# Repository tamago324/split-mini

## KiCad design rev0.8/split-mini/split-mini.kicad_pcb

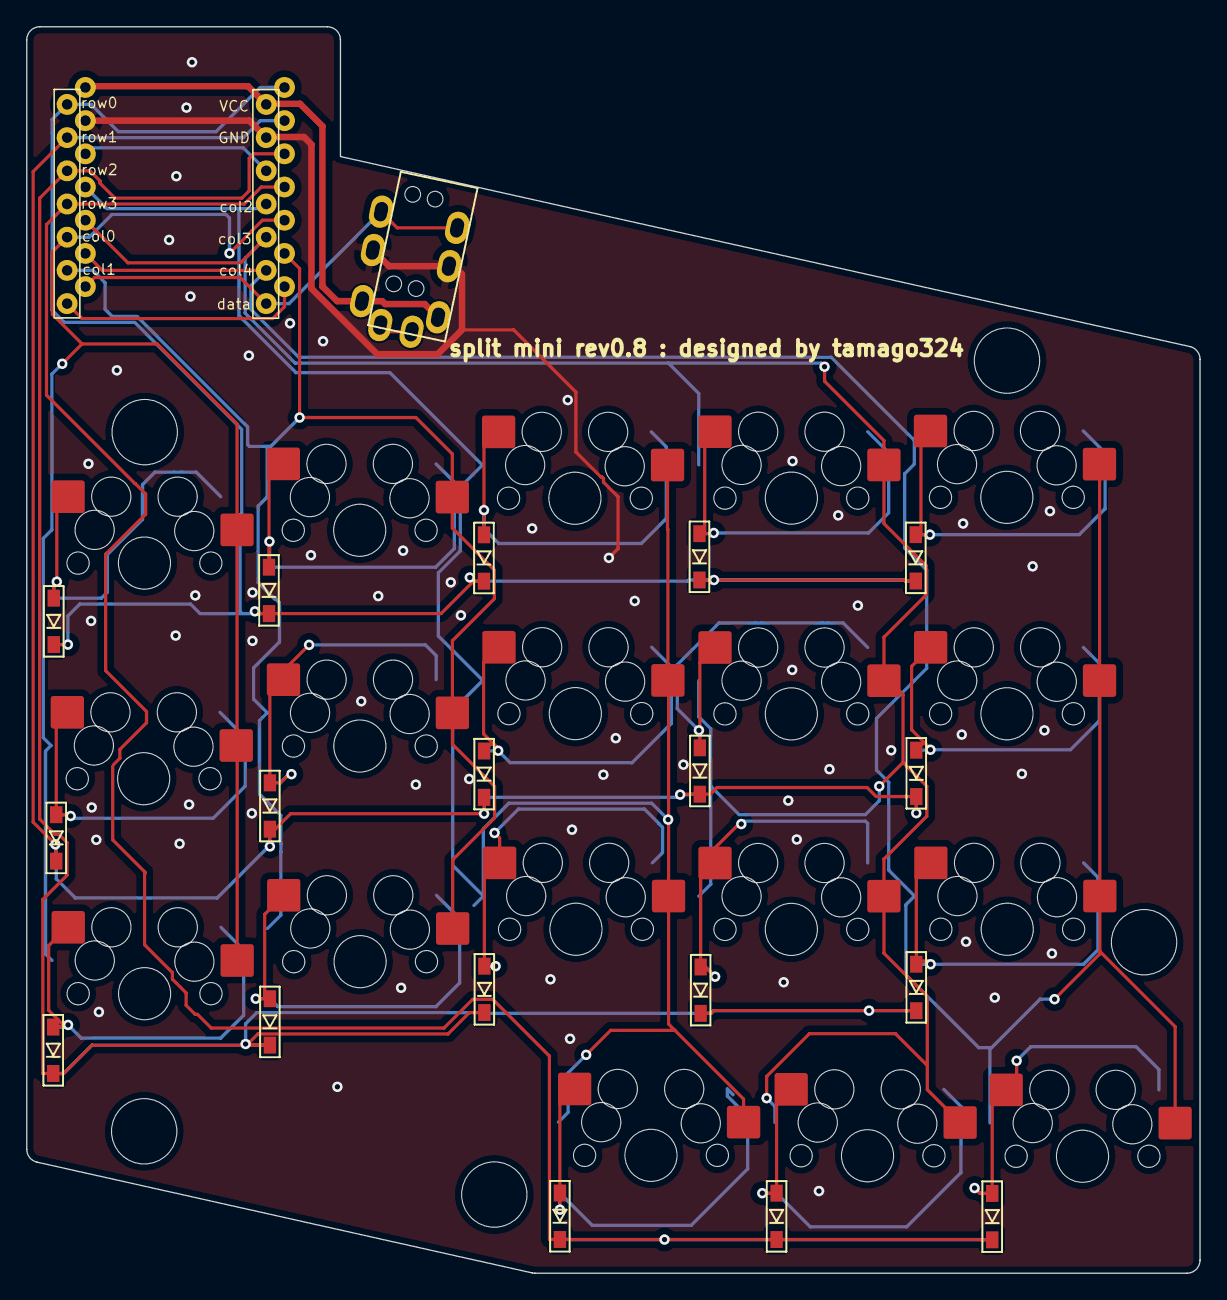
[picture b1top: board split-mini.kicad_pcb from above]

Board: 2 copper layers, 89.8 x 95.4 mm, 43 parts (0 on the bottom side), 30 nets.

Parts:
D1, D2, D3, D4, D5, D6, D7, D8, D9, D10, D11, D12, D13, D14, D15, D16, D17, D18: D; D3_SMD
HOLE1, HOLE2, HOLE3, HOLE5: Val**; M2_HOLE_v2_4.5mm
HOLE4: Val*; M2_HOLE_v2_4.5mm
J1: MJ-4PP-9
SW1, SW2, SW3, SW4, SW5, SW6, SW7, SW8, SW9, SW10, SW11, SW12, SW13, SW14, SW15, SW16, SW17, SW18: SW_PUSH; MX-Hotswap-1U
U1: Seeed Studio XIAO SAMD21; XIAO-RP2040_mod

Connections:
GND: J1.C, U1.13 (GND)
unnamed: D1.2 (A), SW1.2
unnamed: D2.2 (A), SW2.2
unnamed: D3.2 (A), SW3.2
unnamed: D4.2 (A), SW4.2
unnamed: D5.2 (A), SW5.2
unnamed: D6.2 (A), SW6.2
unnamed: D7.2 (A), SW7.2
unnamed: D8.2 (A), SW8.2
unnamed: D9.2 (A), SW9.2
unnamed: D10.2 (A), SW10.2
unnamed: D11.2 (A), SW11.2
unnamed: D12.2 (A), SW12.2
unnamed: D13.2 (A), SW13.2
unnamed: D14.2 (A), SW14.2
unnamed: D15.2 (A), SW15.2
unnamed: D16.2 (A), SW16.2
unnamed: D17.2 (A), SW17.2
unnamed: D18.2 (A), SW18.2
VCC: J1.D, U1.14 (5V)
col0: SW1.1, SW6.1, SW11.1, U1.5 (GP6_SDA)
col1: SW2.1, SW7.1, SW12.1, U1.6 (GP7_SCL)
col2: SW3.1, SW8.1, SW13.1, SW16.1, U1.11 (GP3)
col3: SW4.1, SW9.1, SW14.1, SW17.1, U1.10 (GP4)
col4: SW5.1, SW10.1, SW15.1, SW18.1, U1.9 (GP2)
data: J1.B, U1.8 (GP1_RX)
row0: D1.1 (K), D2.1 (K), D3.1 (K), D4.1 (K), D5.1 (K), U1.1 (GP26)
row1: D6.1 (K), D7.1 (K), D8.1 (K), D9.1 (K), D10.1 (K), U1.2 (GP27)
row2: D11.1 (K), D12.1 (K), D13.1 (K), D14.1 (K), D15.1 (K), U1.3 (GP28)
row3: D16.1 (K), D17.1 (K), D18.1 (K), U1.4 (GP29)

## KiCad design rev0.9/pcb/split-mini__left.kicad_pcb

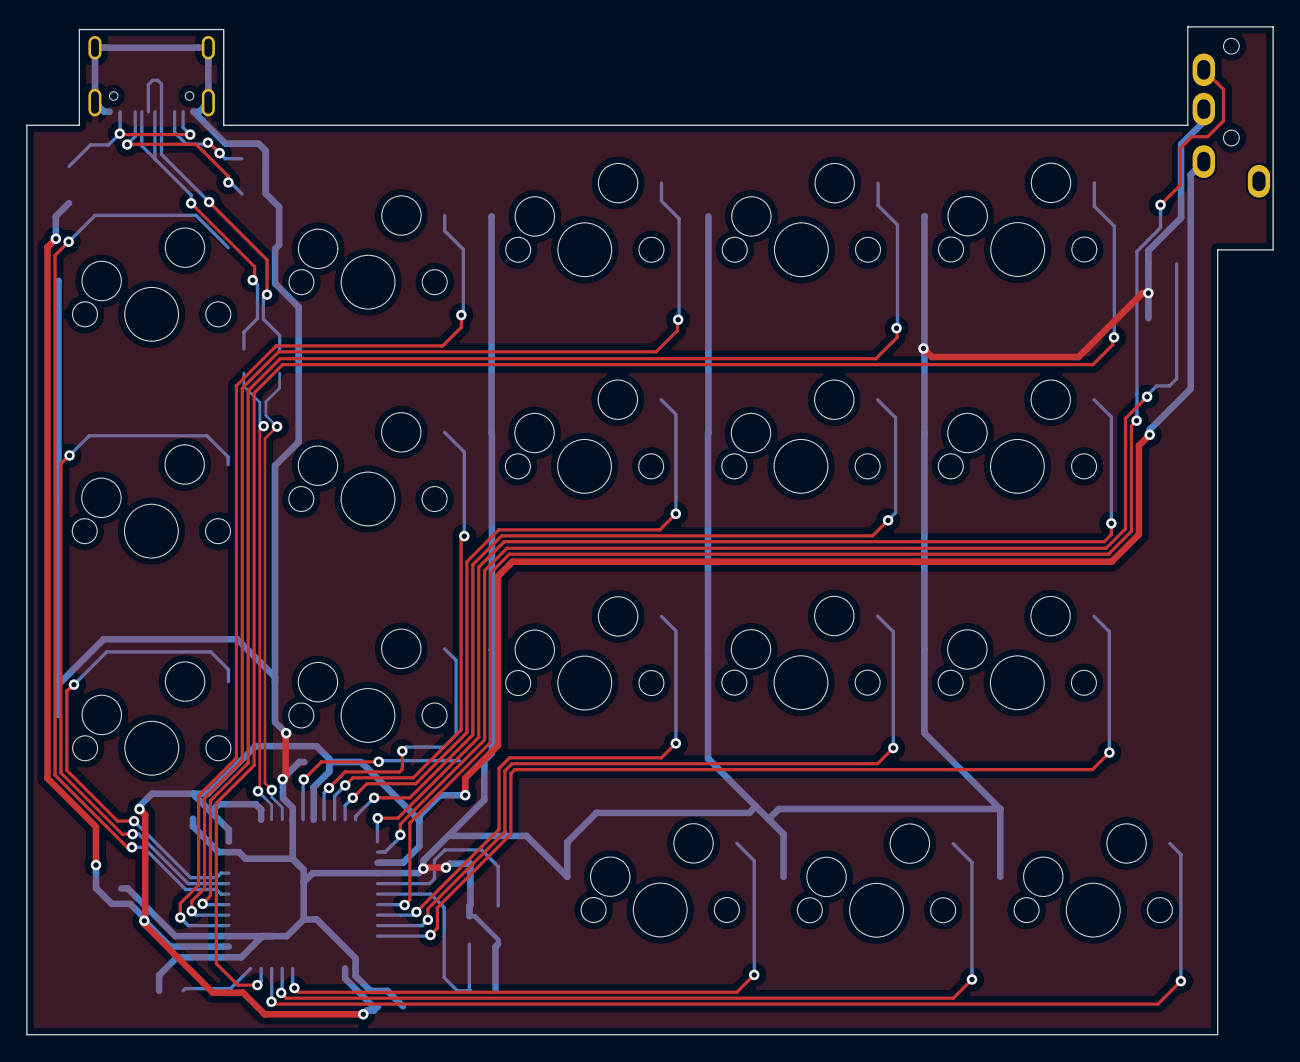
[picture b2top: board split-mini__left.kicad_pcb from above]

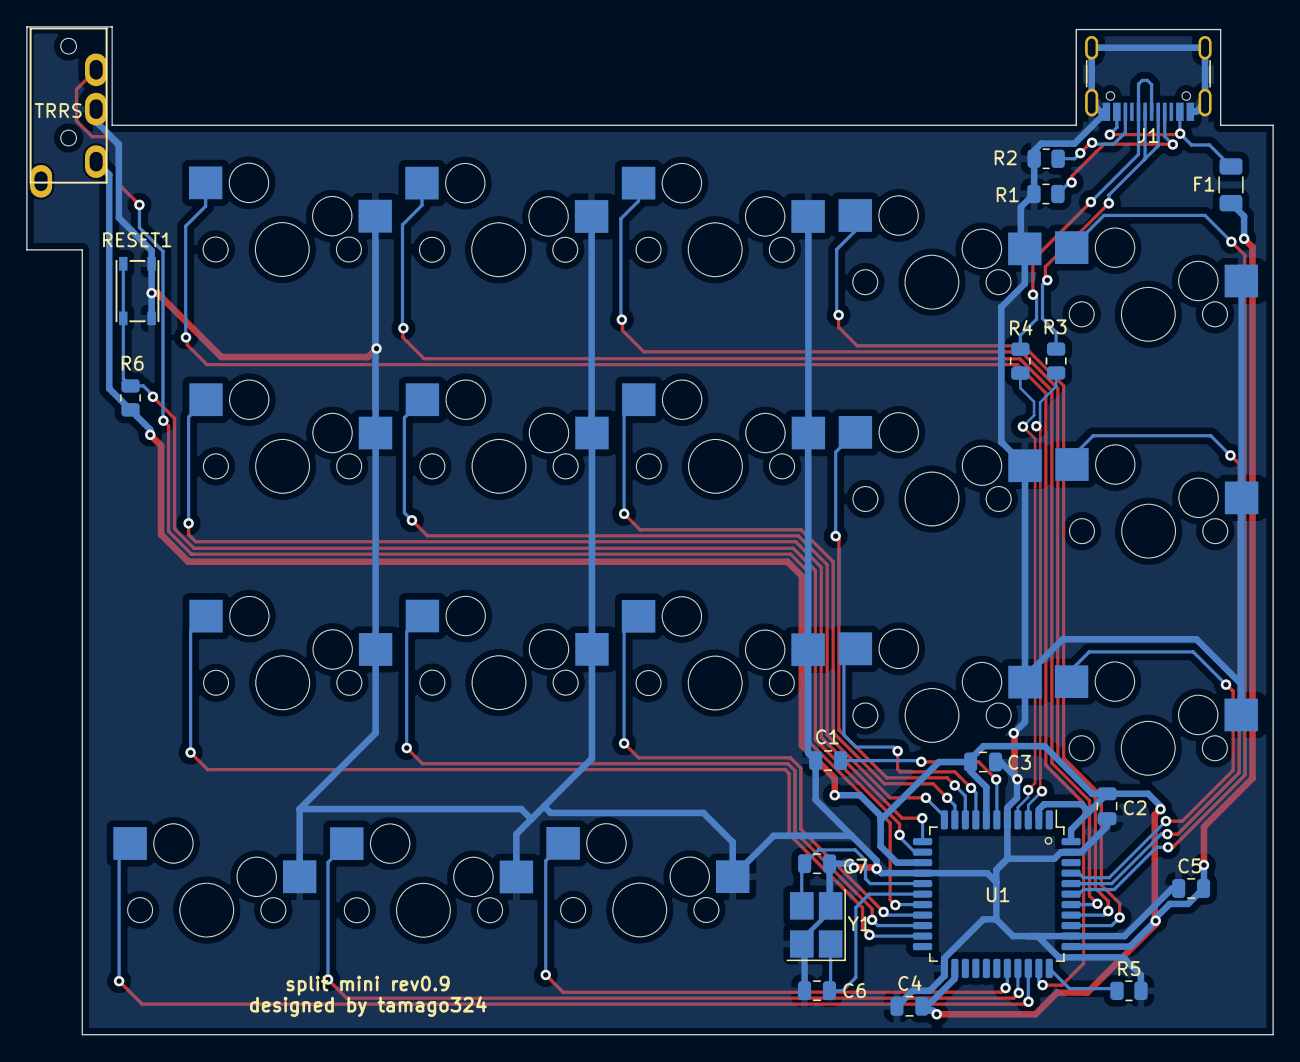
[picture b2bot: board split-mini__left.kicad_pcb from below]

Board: 2 copper layers, 95.0 x 76.8 mm, 37 parts (19 on the bottom side), 33 nets.

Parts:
C1: 1μF; C_0805_2012Metric
C2, C3, C4: 0.1μF; C_0805_2012Metric
C5: 10μF; C_0805_2012Metric
C6, C7: 22pF; C_0805_2012Metric
F1: 500mA; Fuse_1206_3216Metric
J1: USB_C_Receptacle_USB2.0; USB_C_Receptacle_Neltron_5077CR-16SMC2
J2: MJ-4PP-9; MJ-4PP-9_1side
R1, R2: 5.1k; R_0805_2012Metric
R3, R4: 22; R_0805_2012Metric
R5, R6: 10k; R_0805_2012Metric
RESET1: SKRPACE010; SKRPAxE010
SW1, SW2, SW3, SW4, SW5, SW6, SW7, SW8, SW9, SW10, SW11, SW12, SW13, SW14, SW15, SW16, SW17, SW18: SW_Push; CherryMX_Hotswap
U1: ATmega32U4-A; LQFP-44_10x10mm_P0.8mm
Y1: 16MHz; Crystal_SMD_SeikoEpson_FA238-4Pin_3.2x2.5mm_HandSoldering

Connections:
/col0: SW1.2, U1.39 (PF4)
/col1: SW2.2, U1.36 (PF7)
/col2: SW3.2, U1.37 (PF6)
/col3: SW4.2, U1.38 (PF5)
/col4: SW5.2, U1.32 (PC7)
/col5: SW6.2, U1.40 (PF1)
/col6: SW7.2, U1.9 (PB1)
/col7: SW8.2, U1.10 (PB2)
/col8: SW9.2, U1.11 (PB3)
/col9: SW10.2, U1.12 (PB7)
/col10: SW11.2, U1.41 (PF0)
/col11: SW12.2, U1.8 (PB0)
/col12: SW13.2, U1.19 (PD1)
/col13: SW14.2, U1.20 (PD2)
/col14: SW15.2, U1.21 (PD3)
/col15: SW16.2, U1.29 (PB5)
/col16: SW17.2, U1.30 (PB6)
/col17: SW18.2, U1.31 (PC6)
D+: R4.2, U1.4 (D+)
D-: R3.2, U1.3 (D-)
GND: C1.2, C2.2, C3.2, C4.2, C5.2, C6.1, C7.2, J1.A1 (GND), J1.A12 (GND), J1.B1 (GND), J1.B12 (GND), J1.S1 (SHIELD), J2.C, R1.2, R2.2, R5.2, RESET1.1 (A), RESET1.2 (B), SW1.1, SW2.1, SW3.1, SW4.1, SW5.1, SW6.1, SW7.1, SW8.1, SW9.1, SW10.1, SW11.1, SW12.1, SW13.1, SW14.1, SW15.1, SW16.1, SW17.1, SW18.1, U1.5 (UGND), U1.15 (GND), U1.23 (GND), U1.35 (GND), U1.43 (GND), Y1.2, Y1.4
unnamed: C1.1, U1.6 (UCAP)
unnamed: F1.1, J1.A4 (VBUS), J1.A9 (VBUS), J1.B4 (VBUS), J1.B9 (VBUS)
unnamed: J1.A5 (CC1), R1.1
unnamed: J1.A6 (D+), J1.B6 (D+), R4.1
unnamed: J1.A7 (D-), J1.B7 (D-), R3.1
unnamed: J1.B5 (CC2), R2.1
unnamed: R5.1, U1.33 (~HWB/PE2)
RESET: R6.2, RESET1.3 (C), RESET1.4 (D), U1.13 (~RESET)
SCL: J2.B, U1.18 (PD0)
VCC: C2.1, C3.1, C4.1, C5.1, F1.2, J2.D, R6.1, U1.2 (UVCC), U1.7 (VBUS), U1.14 (VCC), U1.24 (AVCC), U1.34 (VCC), U1.44 (AVCC)
XTAL1: C6.2, U1.17 (XTAL1), Y1.1
XTAL2: C7.1, U1.16 (XTAL2), Y1.3
